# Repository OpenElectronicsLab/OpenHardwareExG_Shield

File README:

The OpenHardwareExG_Shield is a platform for ECG, EEG, EMG, ENG, EOG, and
evoked potential applications using an Arduino.

http://openelectronicslab.github.io/OpenHardwareExG_Shield/

Example firmware can be found at:

https://github.com/OpenElectronicsLab/OpenHardwareExG_Shield_Arduino_Library

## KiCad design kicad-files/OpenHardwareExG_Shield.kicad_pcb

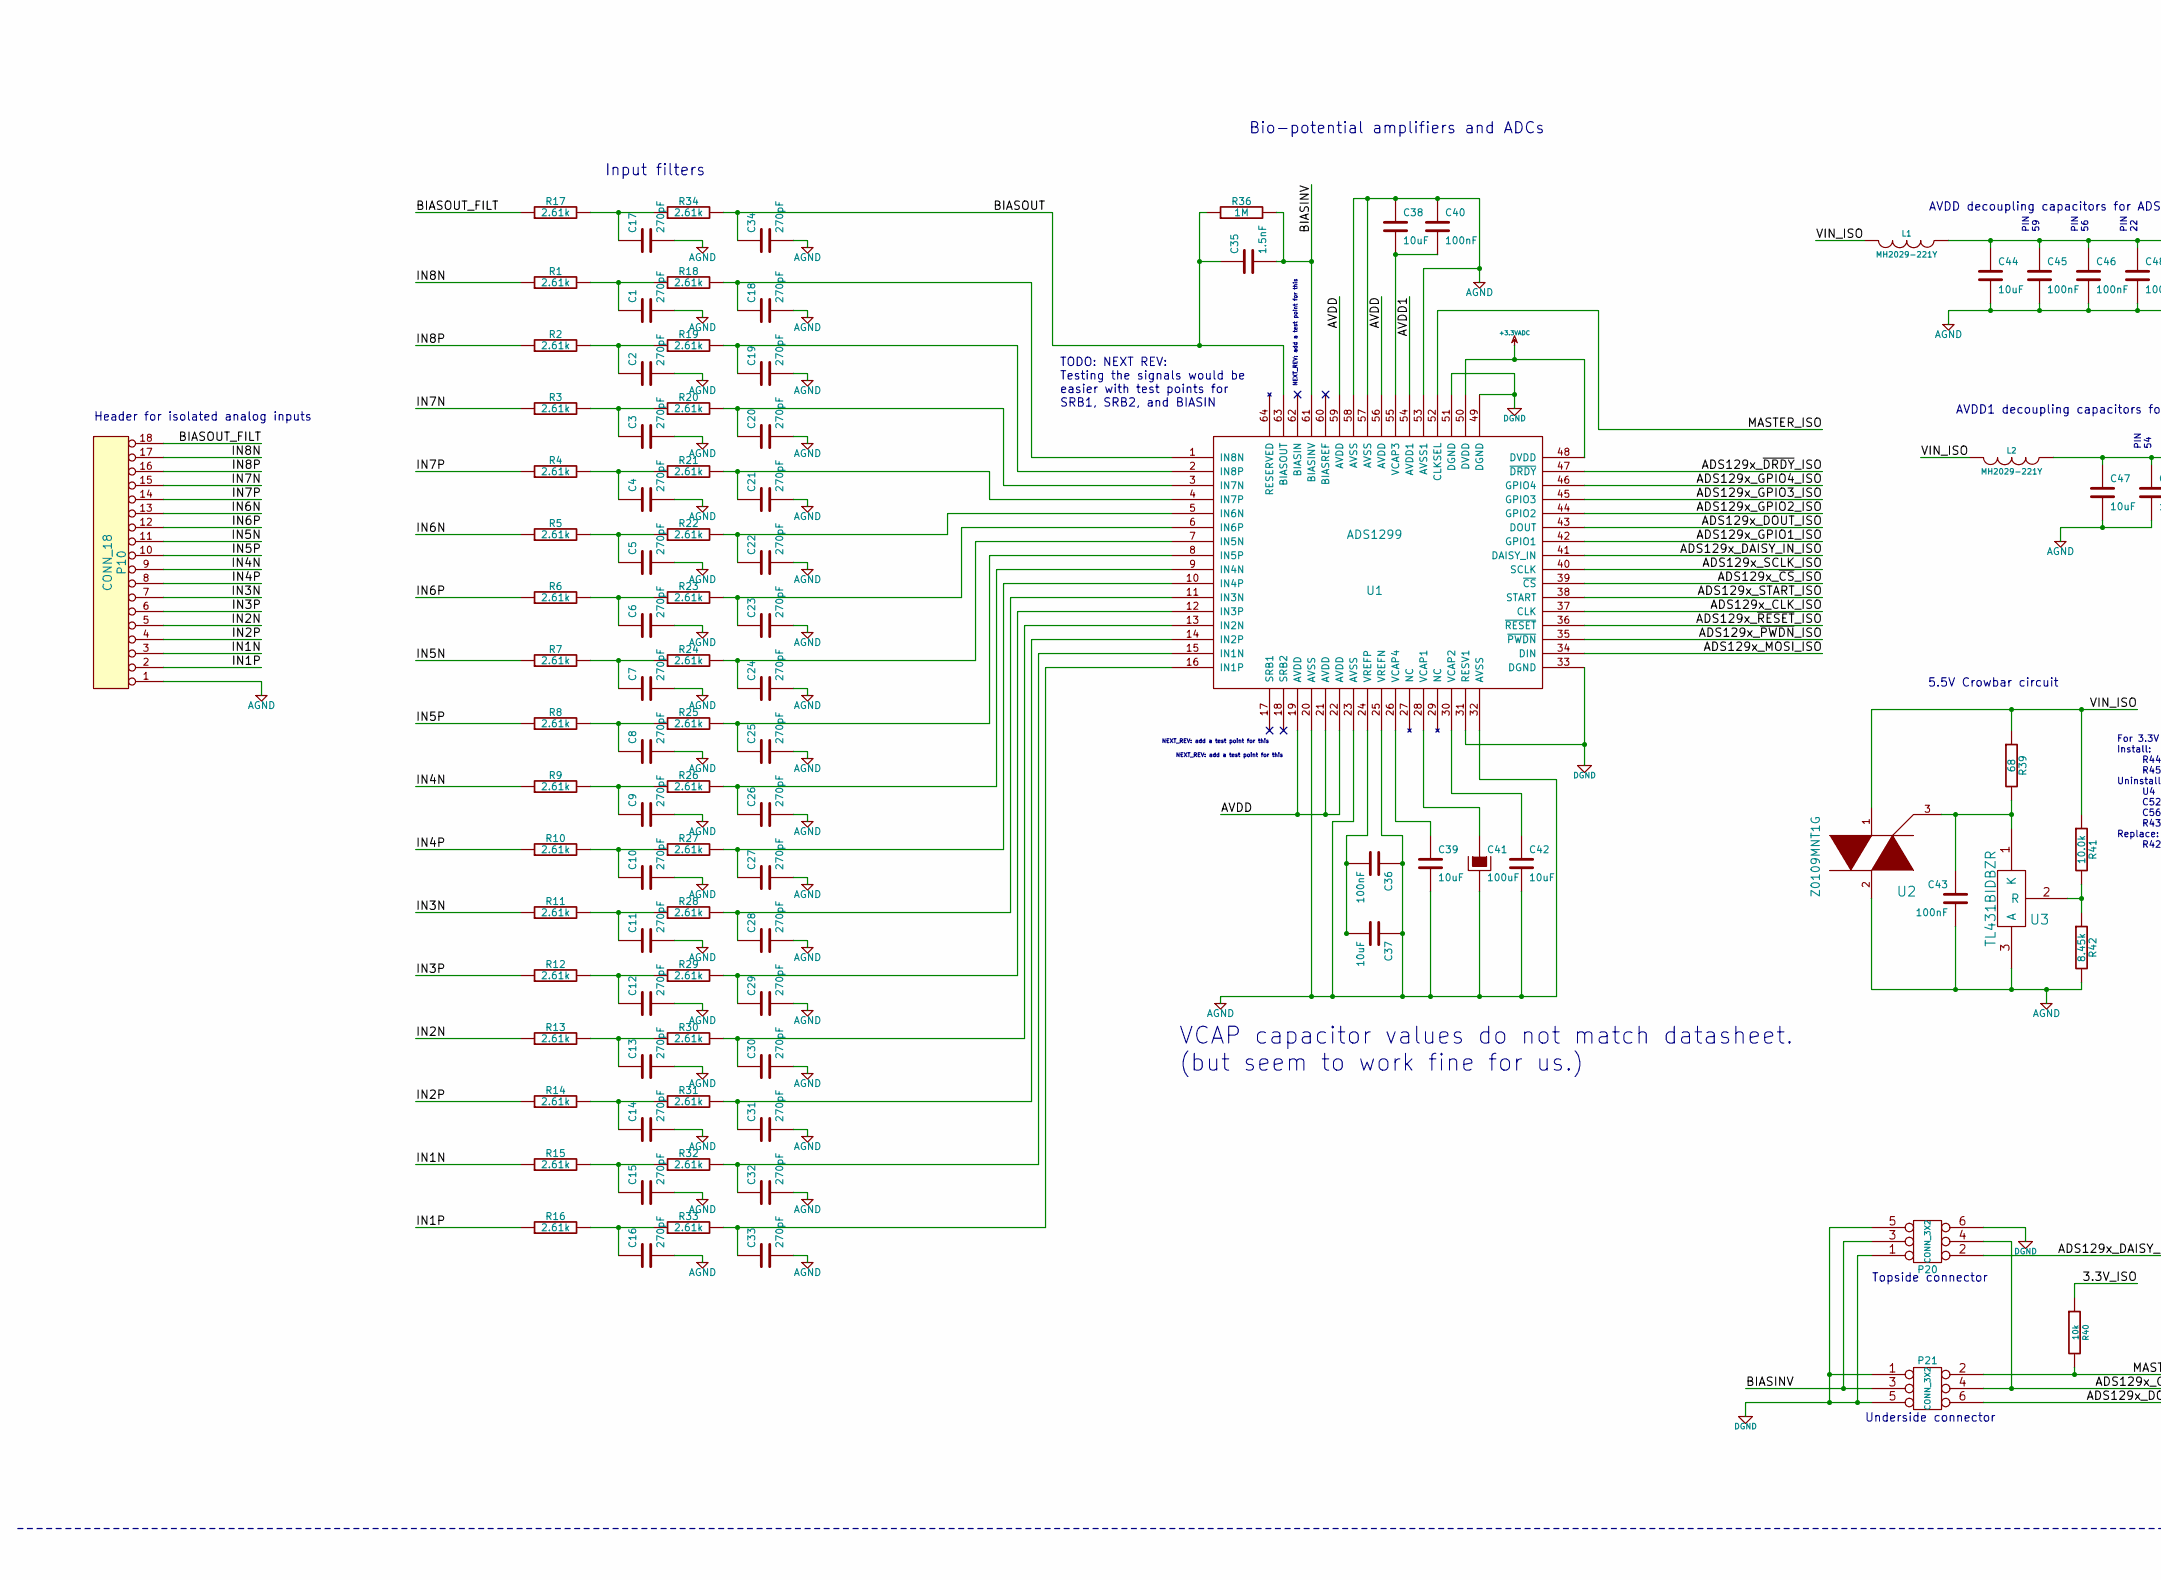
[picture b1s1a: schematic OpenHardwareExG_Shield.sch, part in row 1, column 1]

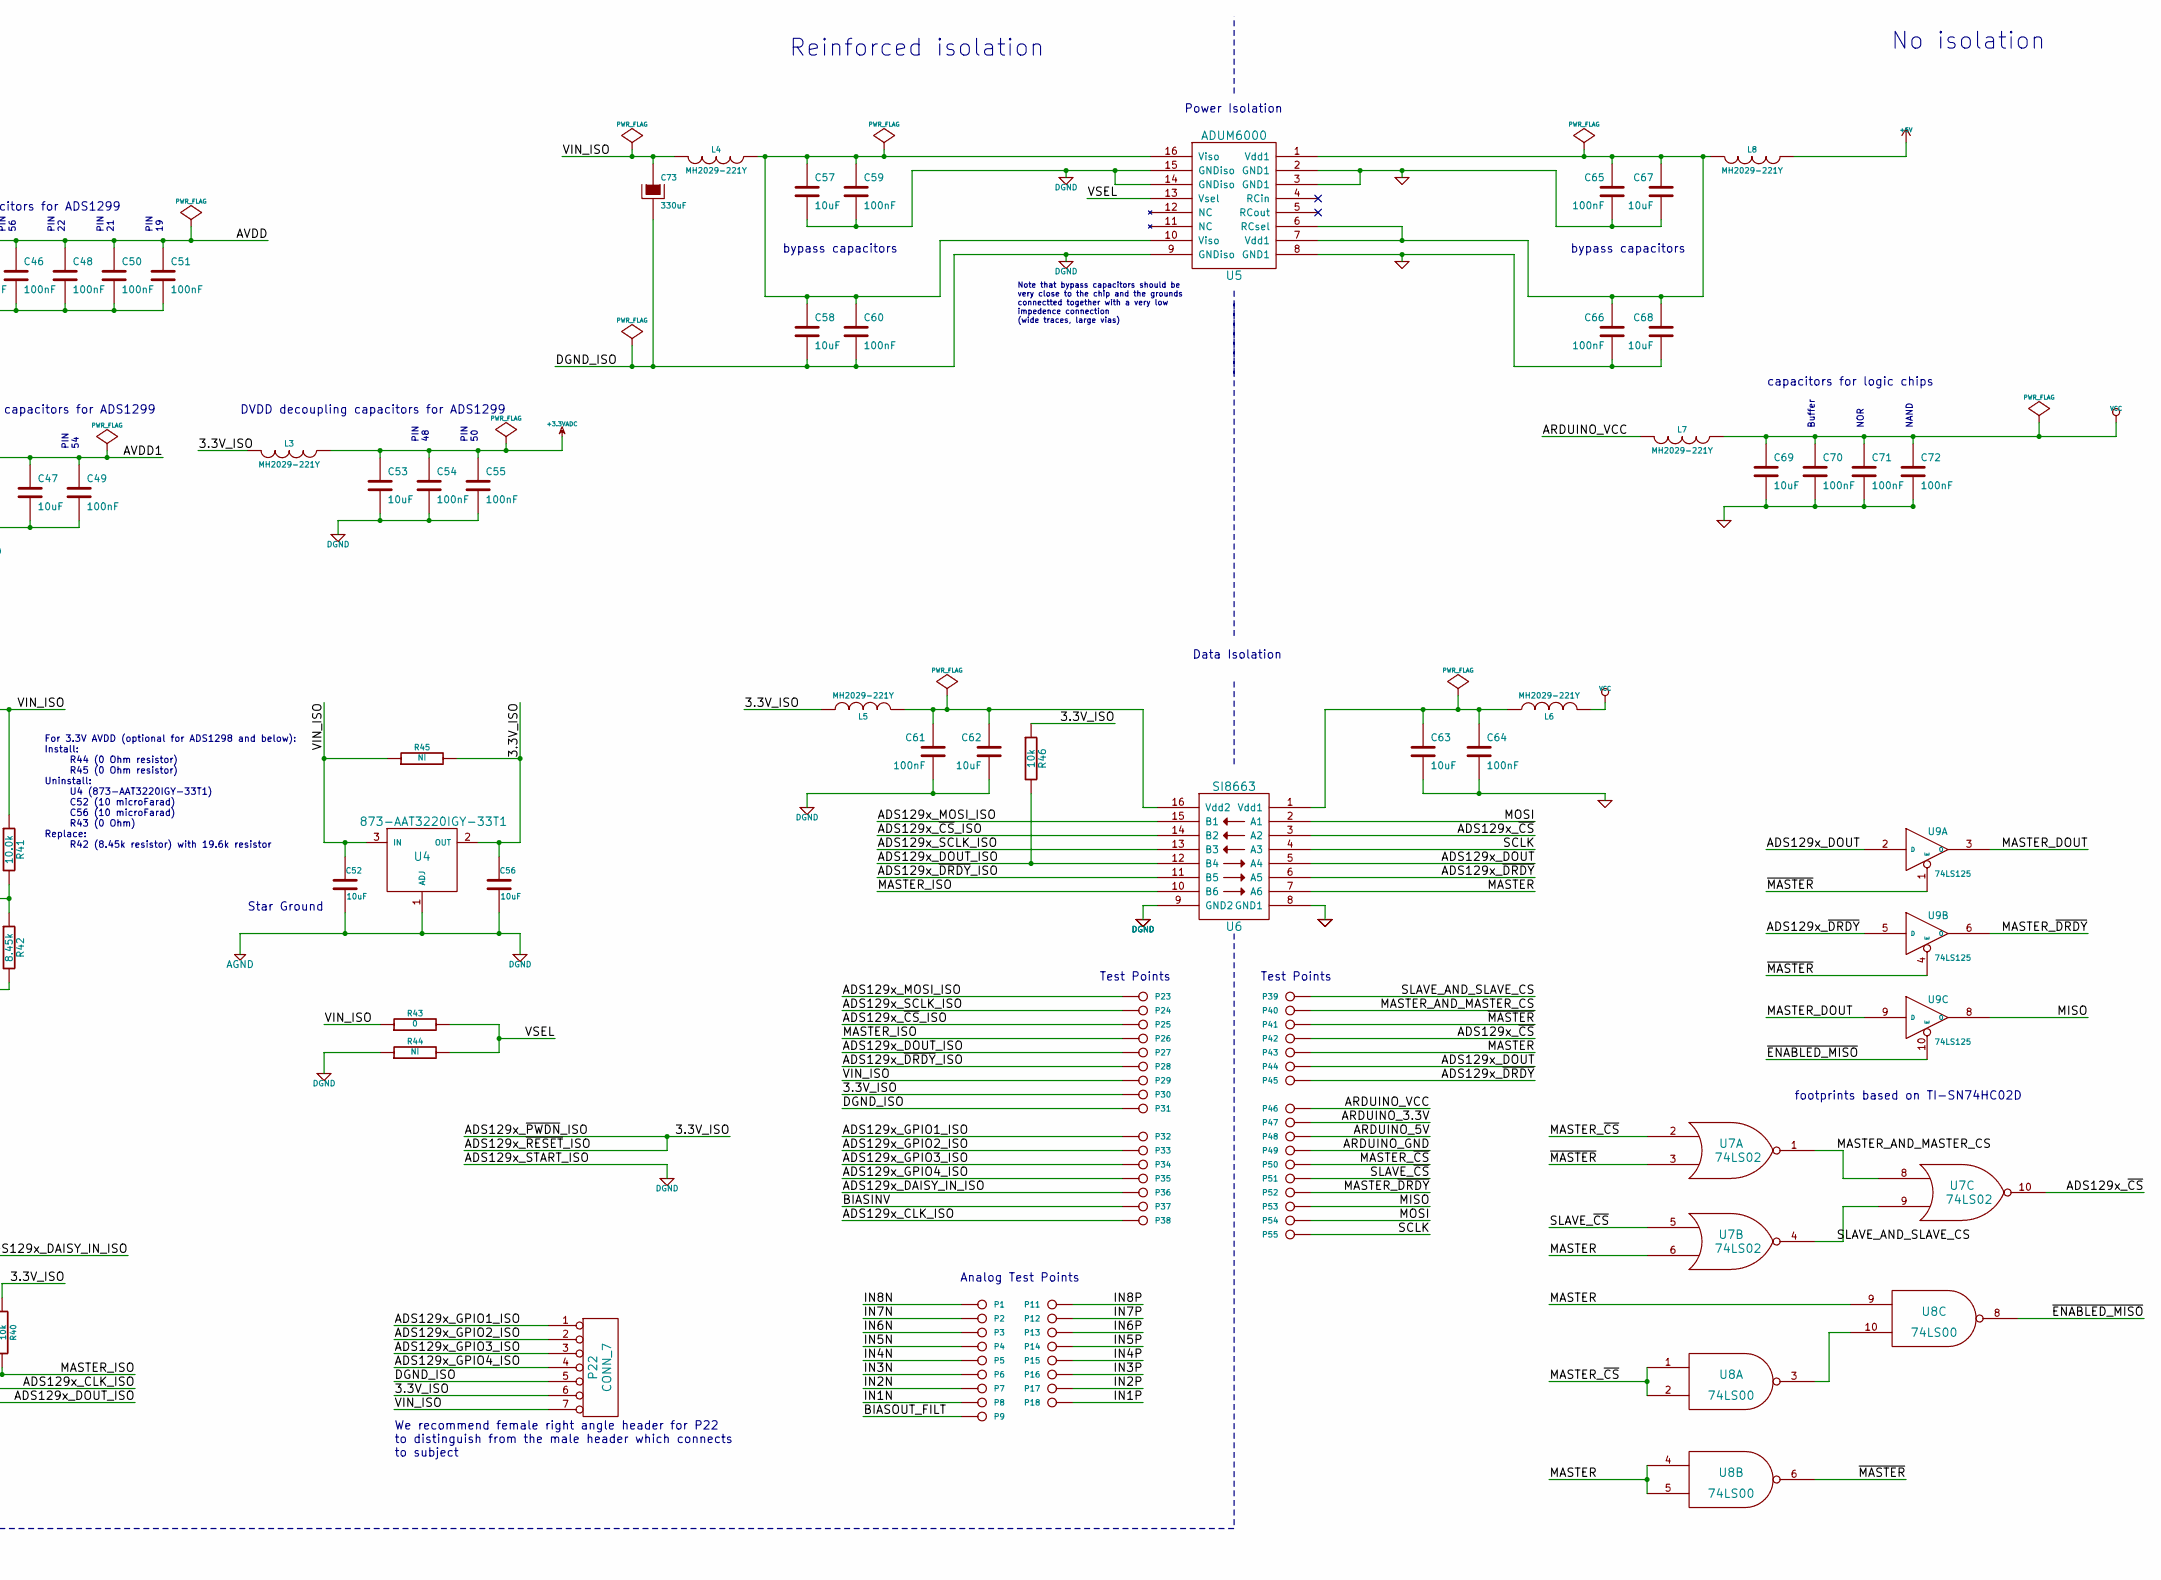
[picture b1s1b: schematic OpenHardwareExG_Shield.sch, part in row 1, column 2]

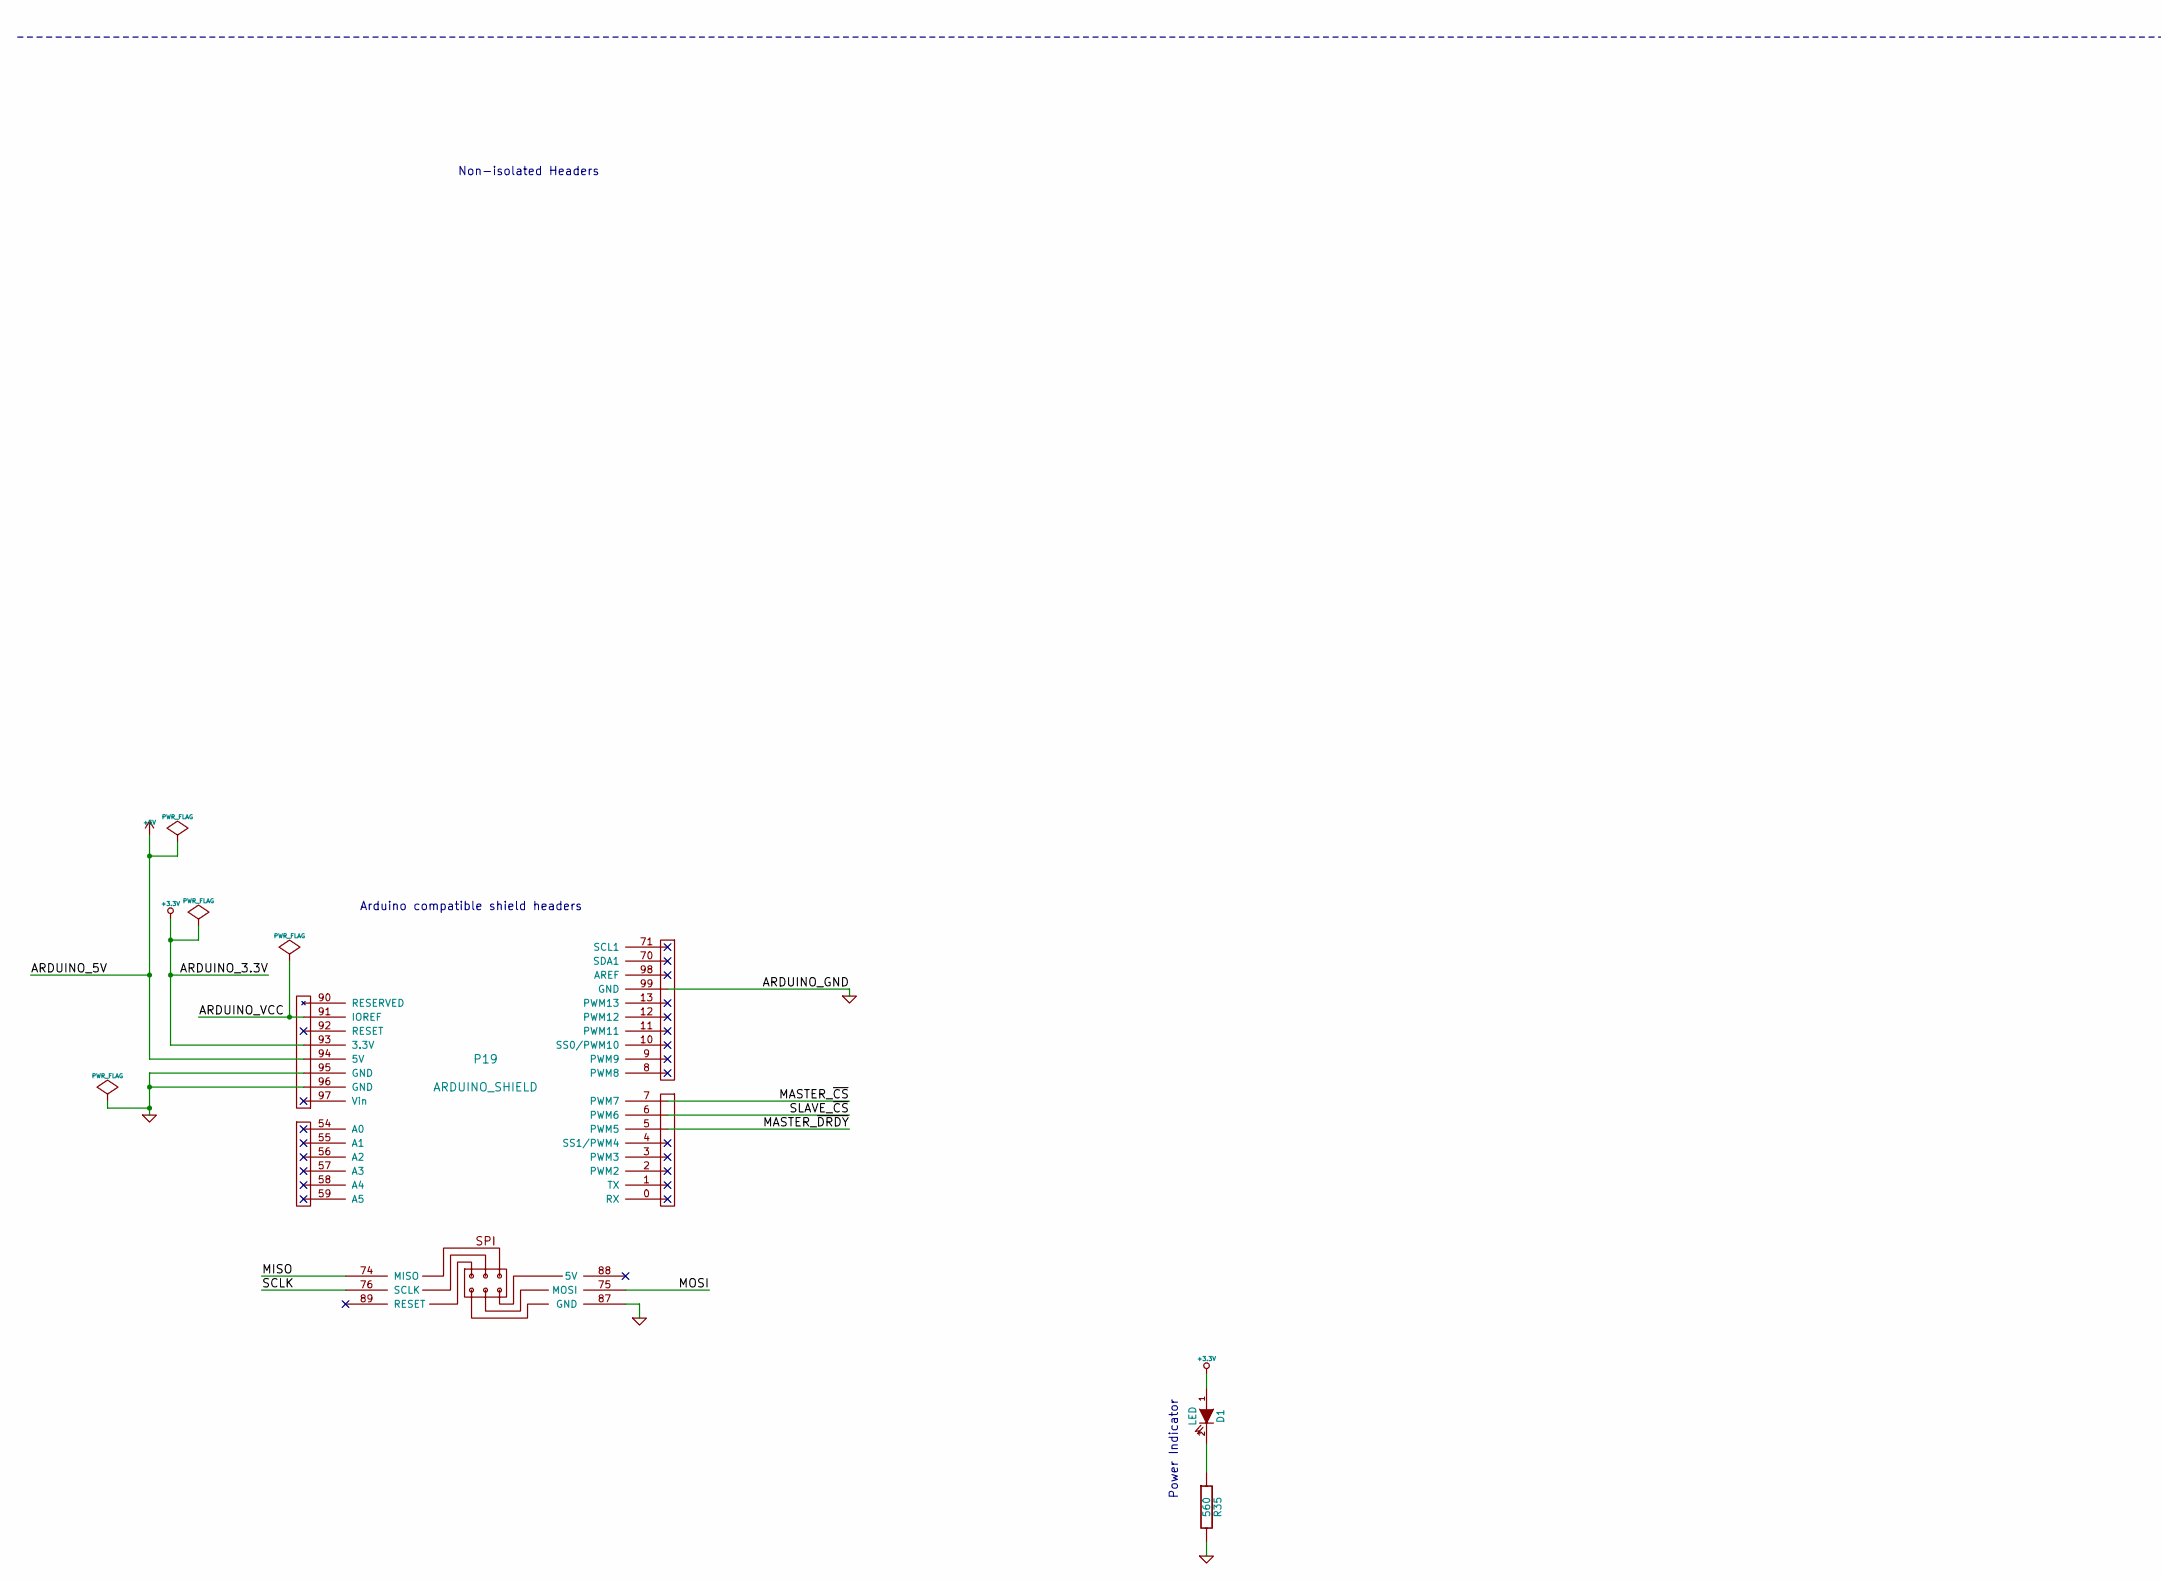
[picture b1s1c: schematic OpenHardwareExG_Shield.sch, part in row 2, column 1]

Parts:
C1, C2, C3, C4, C5, C6, C7, C8, C9, C10, C11, C12, C13, C14, C15, C16, C17, C18, C19, C20, C21, C22, C23, C24, C25, C26, C27, C28, C29, C30, C31, C32, C33, C34: 270pF; SM0603
C35: 1.5nF; SM0603
C36, C40, C43, C45, C46, C48, C49, C50, C51, C54, C55, C59, C60, C61, C64, C65, C66, C70, C71, C72: 100nF; SM0603
C37, C38, C39, C42, C44, C47, C52, C53, C56, C57, C58, C62, C63, C67, C68, C69: 10uF; SM0805
C41: 100uF; SM2512
C73: 330uF; c_tant_D
D1: LED; LED-0603
L1, L2, L3, L4, L5, L6, L7, L8: MH2029-221Y; SM0805
P1, P2, P3, P4, P5, P6, P7, P8, P9, P11, P12, P13, P14, P15, P16, P17, P18, P23, P24, P25, P26, P27, P28, P29, P30, P31, P32, P33, P34, P35, P36, P37, P38, P39, P40, P41, P42, P43, P44, P45, P46, P47, P48, P49, P50, P51, P52, P53, P54, P55: CONN_1; POGO_PAD
P10: CONN_18; PIN_ARRAY_18x1
P19: ARDUINO_SHIELD; arduino_shield_with_holes
P20: CONN_3X2; 54202-G0803ALF
P21: CONN_3X2; 89898-303LF
P22: CONN_7; PIN_ARRAY_7x1
R1, R2, R3, R4, R5, R6, R7, R8, R9, R10, R11, R12, R13, R14, R15, R16, R17, R18, R19, R20, R21, R22, R23, R24, R25, R26, R27, R28, R29, R30, R31, R32, R33, R34: 2.61k; SM0603
R35: 560; SM0603
R36: 1M; SM0805
R39: 68; SM0603
R40, R46: 10k; SM0603
R41: 10.0k; SM0603
R42: 8.45k; SM0603
R43: 0; SM0603
R44, R45: NI; SM0603
U1: ADS1299; TQFP_64
U2: Z0109MNT1G; SOT223
U3: TL431BIDBZR; SOT23
U4: 873-AAT3220IGY-33T1; SOT23
U5: ADUM6000; SO16W
U6: SI8663; SO16W
U7: 74LS02; SO14E
U8: 74LS00; SO14E
U9: 74LS125; SO14E

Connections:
+3.3V: D1.1 (A), P19.93 (3.3V), P47.1
+3.3VADC: C53.1, C54.1, C55.1, L3.1, U1.48 (DVDD), U1.50 (DVDD)
+5V: L8.2, P19.94 (5V), P48.1
/3.3V_ISO: C56.1, L3.2, L5.2, P22.6, P30.1, R40.1, R45.2, R46.1, U1.35 (~PWDN~), U1.36 (~RESET~), U4.2 (OUT)
/ADS129x_CLK_ISO: P20.4, P21.4, P38.1, U1.37 (CLK)
/ADS129x_DAISY_IN_ISO: P20.2, P36.1, U1.41 (DAISY_IN)
/ADS129x_DOUT: P44.1, U6.5 (A4), U9.2 (D)
/ADS129x_DOUT_ISO: P21.6, P27.1, R46.2, U1.43 (DOUT), U6.12 (B4)
/ADS129x_GPIO1_ISO: P22.1, P32.1, U1.42 (GPIO1); also elsewhere on the board
/ADS129x_GPIO2_ISO: P22.2, P33.1, U1.44 (GPIO2); also elsewhere on the board
/ADS129x_GPIO3_ISO: P22.3, P34.1, U1.45 (GPIO3); also elsewhere on the board
/ADS129x_GPIO4_ISO: P22.4, P35.1, U1.46 (GPIO4); also elsewhere on the board
/ADS129x_MOSI_ISO: P23.1, U1.34 (DIN), U6.15 (B1)
/ADS129x_SCLK_ISO: P24.1, U1.40 (SCLK), U6.13 (B3)
/ADS129x_~CS~: P42.1, U6.3 (A2), U7.10
/ADS129x_~CS~_ISO: P25.1, U1.39 (~CS~), U6.14 (B2)
/ADS129x_~DRDY~: P45.1, U6.6 (A5), U9.5 (D)
/ADS129x_~DRDY~_ISO: P28.1, U1.47 (~DRDY~), U6.11 (B5)
/ARDUINO_VCC: L7.2, P19.91 (IOREF), P46.1
/AVDD: C44.1, C45.1, C46.1, C48.1, C50.1, C51.1, L1.1, U1.19 (AVDD), U1.21 (AVDD), U1.22 (AVDD), U1.56 (AVDD), U1.59 (AVDD)
/AVDD1: C47.1, C49.1, L2.1, U1.54 (AVDD1)
/BIASINV: C35.2, P20.3, P21.3, P37.1, R36.2, U1.61 (BIASINV)
/BIASOUT: C34.1, C35.1, R34.2, R36.1, U1.63 (BIASOUT)
/BIASOUT_FILT: P9.1, P10.18, R17.1
/IN1N: P8.1, P10.3, R15.1
/IN1P: P10.2, P18.1, R16.1
/IN2N: P7.1, P10.5, R13.1
/IN2P: P10.4, P17.1, R14.1
/IN3N: P6.1, P10.7, R11.1
/IN3P: P10.6, P16.1, R12.1
/IN4N: P5.1, P10.9, R9.1
/IN4P: P10.8, P15.1, R10.1
/IN5N: P4.1, P10.11, R7.1
/IN5P: P10.10, P14.1, R8.1
/IN6N: P3.1, P10.13, R5.1
/IN6P: P10.12, P13.1, R6.1
/IN7N: P2.1, P10.15, R3.1
/IN7P: P10.14, P12.1, R4.1
/IN8N: P1.1, P10.17, R1.1
/IN8P: P10.16, P11.1, R2.1
/MASTER: P43.1, U6.7 (A6), U7.6, U8.4, U8.5, U8.9
/MASTER_AND_MASTER_CS: P40.1, U7.1, U7.8
/MASTER_DOUT: U9.3 (O), U9.9 (D)
/MASTER_ISO: P21.2, P26.1, R40.2, U1.52 (CLKSEL), U6.10 (B6)
/MASTER_~CS~: P19.7 (PWM7), P50.1, U7.2, U8.1, U8.2
/MASTER_~DRDY~: P19.5 (PWM5), P52.1, U9.6 (O)
/MISO: P19.74 (MISO), P53.1, U9.8 (O)
/MOSI: P19.75 (MOSI), P54.1, U6.2 (A1)
/SCLK: P19.76 (SCLK), P55.1, U6.4 (A3)
/SLAVE_AND_SLAVE_CS: P39.1, U7.4, U7.9
/SLAVE_~CS~: P19.6 (PWM6), P51.1, U7.5
/VIN_ISO: C52.1, C73.1, L1.2, L2.2, L4.2, P22.7, P29.1, R39.1, R41.1, R43.1, R45.1, U2.1, U4.3 (IN)
/VSEL: R43.2, R44.2, U5.13 (Vsel)
/~ENABLED_MISO~: U8.8, U9.10 (E)
/~MASTER~: P41.1, U7.3, U8.6, U9.1 (E), U9.4 (E)
AGND: C1.2, C2.2, C3.2, C4.2, C5.2, C6.2, C7.2, C8.2, C9.2, C10.2, C11.2, C12.2, C13.2, C14.2, C15.2, C16.2, C17.2, C18.2, C19.2, C20.2, C21.2, C22.2, C23.2, C24.2, C25.2, C26.2, C27.2, C28.2, C29.2, C30.2, C31.2, C32.2, C33.2, C34.2, C36.1, C37.1, C38.1, C39.2, C40.1, C41.2, C42.2, C43.2, C44.2, C45.2, C46.2, C47.2, C48.2, C49.2, C50.2, C51.2, C52.2, C53.2, C54.2, C55.2, C56.2, C57.2, C58.2, C59.2, C60.2, C61.2, C62.2, C73.2, P10.1, P20.1, P20.5, P20.6, P21.1, P21.5, P22.5, P31.1, R42.2, R44.1, U1.20 (AVSS), U1.23 (AVSS), U1.25 (VREFN), U1.31 (RESV1), U1.32 (AVSS), U1.33 (DGND), U1.38 (START), U1.49 (DGND), U1.51 (DGND), U1.53 (AVSS1), U1.57 (AVSS), U1.58 (AVSS), U2.2, U3.3 (A), U4.1 (ADJ), U5.9 (GNDiso), U5.14 (GNDiso), U5.15 (GNDiso), U6.9 (GND2); also elsewhere on the board
GND: C63.2, C64.2, C65.2, C66.2, C67.2, C68.2, C69.2, C70.2, C71.2, C72.2, P19.87 (GND), P19.95 (GND), P19.96 (GND), P19.99 (GND), P49.1, R35.2, U5.2 (GND1), U5.3 (GND1), U5.8 (GND1), U6.8 (GND1), U7.7 (GND), U8.7 (GND), U9.7 (GND)
unnamed: C1.1, R1.2, R18.1
unnamed: C2.1, R2.2, R19.1
unnamed: C3.1, R3.2, R20.1
unnamed: C4.1, R4.2, R21.1
unnamed: C5.1, R5.2, R22.1
unnamed: C6.1, R6.2, R23.1
unnamed: C7.1, R7.2, R24.1
unnamed: C8.1, R8.2, R25.1
unnamed: C9.1, R9.2, R26.1
unnamed: C10.1, R10.2, R27.1
unnamed: C11.1, R11.2, R28.1
unnamed: C12.1, R12.2, R29.1
unnamed: C13.1, R13.2, R30.1
unnamed: C14.1, R14.2, R31.1
unnamed: C15.1, R15.2, R32.1
unnamed: C16.1, R16.2, R33.1
unnamed: C17.1, R17.2, R34.1
unnamed: C18.1, R18.2, U1.1 (IN8N)
unnamed: C19.1, R19.2, U1.2 (IN8P)
unnamed: C20.1, R20.2, U1.3 (IN7N)
unnamed: C21.1, R21.2, U1.4 (IN7P)
unnamed: C22.1, R22.2, U1.5 (IN6N)
unnamed: C23.1, R23.2, U1.6 (IN6P)
unnamed: C24.1, R24.2, U1.7 (IN5N)
unnamed: C25.1, R25.2, U1.8 (IN5P)
unnamed: C26.1, R26.2, U1.9 (IN4N)
unnamed: C27.1, R27.2, U1.10 (IN4P)
unnamed: C28.1, R28.2, U1.11 (IN3N)
unnamed: C29.1, R29.2, U1.12 (IN3P)
unnamed: C30.1, R30.2, U1.13 (IN2N)
unnamed: C31.1, R31.2, U1.14 (IN2P)
unnamed: C32.1, R32.2, U1.15 (IN1N)
unnamed: C33.1, R33.2, U1.16 (IN1P)
unnamed: C36.2, C37.2, U1.24 (VREFP)
unnamed: C38.2, C40.2, U1.55 (VCAP3)
unnamed: C39.1, U1.26 (VCAP4)
unnamed: C41.1, U1.28 (VCAP1)
unnamed: C42.1, U1.30 (VCAP2)
unnamed: C43.1, R39.2, U2.3, U3.1 (K)
unnamed: C57.1, C58.1, C59.1, C60.1, L4.1, U5.10 (Viso), U5.16 (Viso)
unnamed: C61.1, C62.1, L5.1, U6.16 (Vdd2)
unnamed: C63.1, C64.1, L6.1, U6.1 (Vdd1)
unnamed: C65.1, C66.1, C67.1, C68.1, L8.1, U5.1 (Vdd1), U5.6 (RCsel), U5.7 (Vdd1)
unnamed: D1.2 (K), R35.1
unnamed: R41.2, R42.1, U3.2 (R)
unnamed: U8.3, U8.10
VCC: C69.1, C70.1, C71.1, C72.1, L6.2, L7.1, U7.14 (VCC), U8.14 (VCC), U9.14 (VCC)

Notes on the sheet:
Power Indicator
Non-isolated Headers
Arduino compatible shield headers
Header for isolated analog inputs
Input filters
Bio-potential amplifiers and ADCs
5.5V Crowbar circuit
No isolation
Reinforced isolation
PIN 48
PIN 50
DVDD decoupling capacitors for ADS1299
Data Isolation
Power Isolation
AVDD1 decoupling capacitors for ADS1299
PIN 54
PIN 19
PIN 21
PIN 22
PIN 56
PIN 59
AVDD decoupling capacitors for ADS1299
Underside connector
Topside connector
NAND
NOR
Buffer
capacitors for logic chips
Note that bypass capacitors should be very close to the chip and the grounds connectted together with a very low impedence connection (wide traces, large vias)
bypass capacitors
Test Points
Analog Test Points
footprints based on TI-SN74HC02D
Star Ground
For 3.3V AVDD (optional for ADS1298 and below): Install: R44 (0 Ohm resistor) R45 (0 Ohm resistor) Uninstall: U4 (873-AAT3220IGY-33T1) C52 (10 microFarad) C56 (10 microFarad) R43 (0 Ohm) Replace: R42 (8.45k resistor) with 19.6k resistor
VCAP capacitor values do not match datasheet. (but seem to work fine for us.)
We recommend female right angle header for P22 to distinguish from the male header which connects to subject
NEXT_REV: add a test point for this
TODO: NEXT REV: Testing the signals would be easier with test points for SRB1, SRB2, and BIASIN

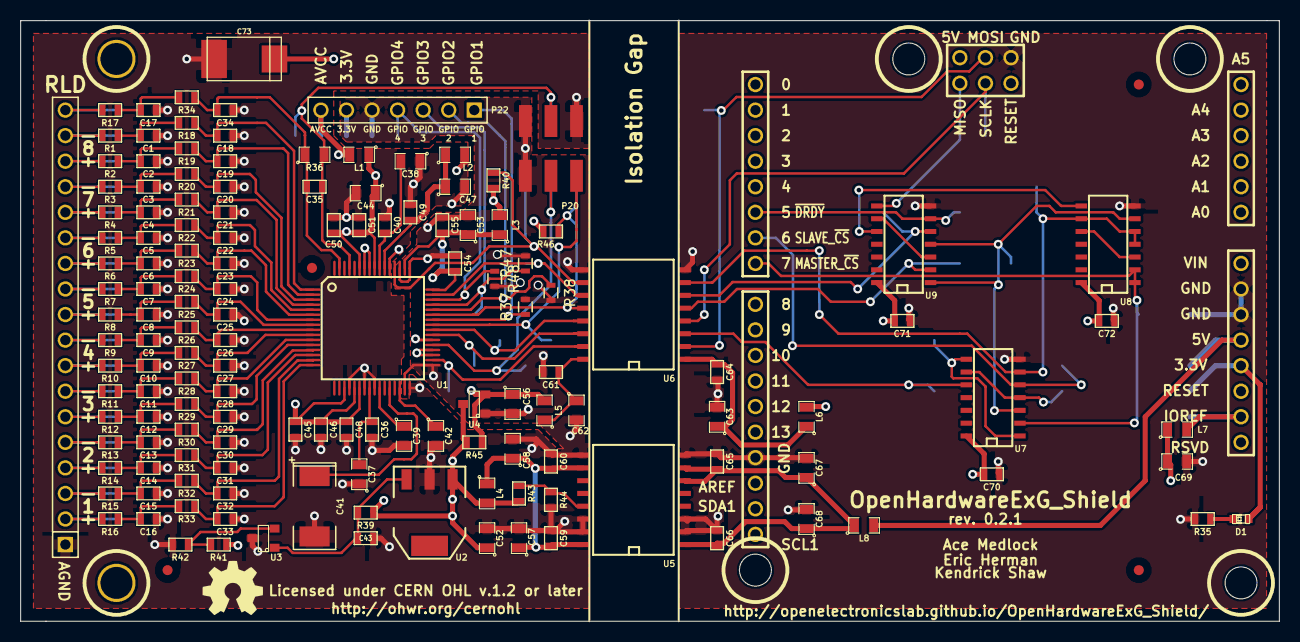
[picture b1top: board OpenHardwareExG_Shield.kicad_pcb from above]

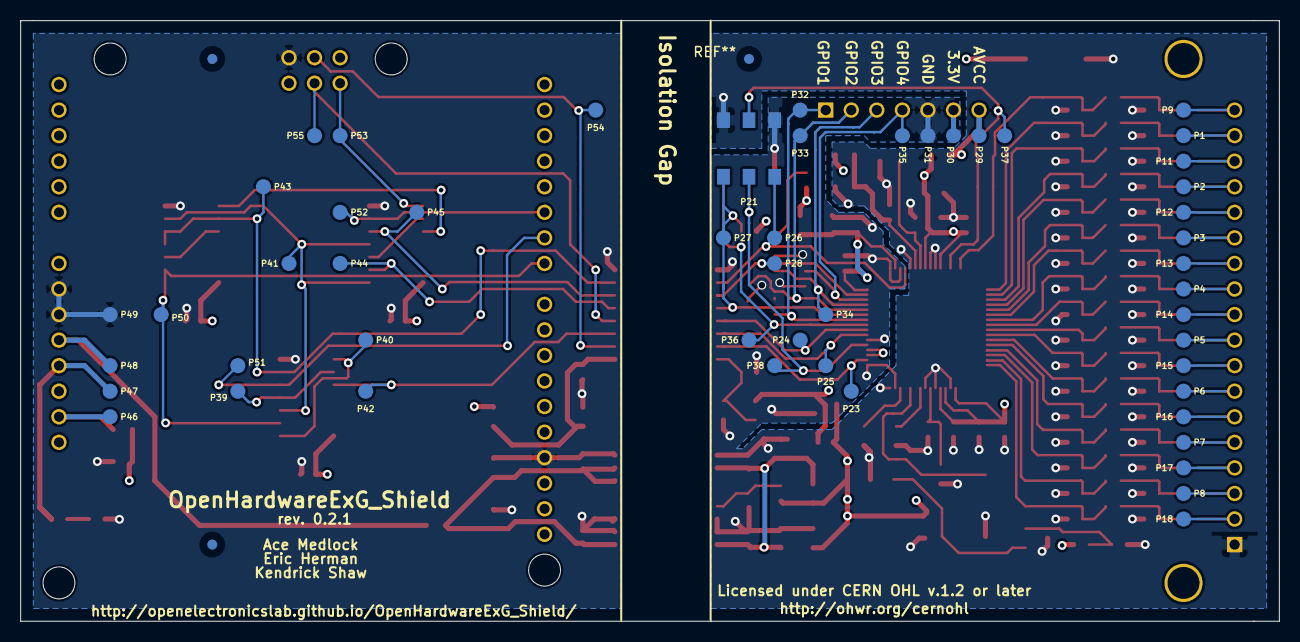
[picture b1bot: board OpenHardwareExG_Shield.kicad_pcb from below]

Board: 4 copper layers, 125.1 x 59.7 mm, 196 parts (51 on the bottom side), 104 nets.

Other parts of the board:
Hole_M3, Hole_M3#2: VAL**; Hole_M3
R37, R38, R47, R48: 10k; R_0603

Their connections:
/ADS129x_GPIO1_ISO: R37.1; also elsewhere on the board
/ADS129x_GPIO2_ISO: R38.1; also elsewhere on the board
/ADS129x_GPIO3_ISO: R47.1; also elsewhere on the board
/ADS129x_GPIO4_ISO: R48.1; also elsewhere on the board
AGND: R37.2, R38.2, R47.2, R48.2; also elsewhere on the board

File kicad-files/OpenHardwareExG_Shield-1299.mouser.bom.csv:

mfg part number  ,  quantity 1  ,  Description  ,  Customer Part No.
VJ0805A271KXBPW1BC  ,  34  ,  270pF  ,  C1-34
CGA3E2X7R1H152K080AA  ,  1  ,  1.5nF  ,  C35
VJ0603Y104JXJPW1BC  ,  19  ,  100nF  ,  C36_C40_C45-46_C48-51_C54-55_C59-61_C64-66_C70-72
GRM21BR71A106KA73L  ,  17  ,  10uF  ,  C37-39_C42-44_C47_C52-53_C56-58_C62-63_C67-69
593D107X9010C2TE3  ,  1  ,  100uF  ,  C41
LG Q971-KN-1  ,  1  ,  LED  ,  D1
MH2029-221Y  ,  8  ,  MH2029-221Y  ,  L1-8
68021-120HLF  ,  1  ,  CONN_10X2  ,  P10
54202-G0803ALF  ,  1  ,  CONN_3X2  ,  P20
89898-303LF  ,  1  ,  CONN_3X2  ,  P21
RR1220P-2611-D-M  ,  34  ,  2.61k  ,  R1-34
CRCW0603560RJNEA  ,  1  ,  560  ,  R35
RR1220P-105-D  ,  1  ,  1M  ,  R36
CRCW060347R0FKEA  ,  6  ,  47  ,  R37-38_R47-50
CRCW060368R0JNEA  ,  1  ,  68  ,  R39
RR0816P-103-D  ,  3  ,  10k  ,  R40-41_R46
RR0816P-8451-D-90H  ,  1  ,  8.45k  ,  R42
CRCW06030000Z0EB  ,  1  ,  0  ,  R43
ADS1299IPAG  ,  1  ,  ADS1299  ,  U1
Z0109MNT1G  ,  1  ,  Z0109MNT1G  ,  U2
771-TL431BIDBZR215  ,  1  ,  TL431BIDBZR  ,  U3
873-AAT3220IGY-33T1  ,  1  ,  873-AAT3220IGY-33T1  ,  U4
ADUM6000ARIZ  ,  1  ,  ADUM6000  ,  U5
Si8663BD-B-IS  ,  1  ,  SI8663  ,  U6
MC74HC02ADG  ,  1  ,  74LS02  ,  U7
MC74HC00ADR2G  ,  1  ,  74LS00  ,  U8
MC74HC125ADG  ,  1  ,  74LS125  ,  U9

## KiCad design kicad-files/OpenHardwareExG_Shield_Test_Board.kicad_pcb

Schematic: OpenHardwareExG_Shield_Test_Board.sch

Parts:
C1, C5, C10, C11: 10uF; SM0805
C2, C3, C4, C6, C7, C8, C9, C12: 100nF; SM0603
D1, D2, D3: LED; LED-0603
L1, L3, L4: MH2029-221Y; SM0805
P1, P2, P3, P4, P5, P6, P7, P8, P9, P11, P12, P13, P14, P15, P16, P17, P18, P23, P24, P25, P26, P27, P28, P29, P30, P31, P32, P33, P34, P35, P36, P37, P38, P39, P40, P41, P42, P43, P44, P45, P46, P47, P48, P49, P50, P51, P52, P53, P54, P55: CONN_1; POGO_PIN_BASE
P19: ARDUINO_SHIELD; arduino_shield_with_holes
P56: CONN_3X2; pin_array_3x2
P57: CONN_20X2; PIN_ARRAY_20X2
R1, R3, R5, R43, R44: 10k; SM0603
R2, R4, R6: 1k; SM0603
R7: 5.1K; SM0603
R8, R18, R19, R20, R21, R22, R23, R24, R25, R26, R27, R28, R29, R30, R31, R32: 100; SM0603
R9, R10, R11, R12, R13, R14, R15, R16, R34, R35, R36, R37, R38, R39: 1M; SM0805
R17, R33: 15k; SM0603
R40, R41, R42: 560; SM0603
SW1: SW_PUSH; smt-tactile-button
U1, U2, U4: 74HC165; SO16E
U3: 74HC595PWR; TSSOP16
U5: 74LS125; SO14E
U6: TPS2095D; SO16E
U8: SI8661; SO16W

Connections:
+3.3V: P19.93 (3.3V), U6.3 (IN2)
+5V: P19.88 (5V), P19.94 (5V), P56.4, U6.6 (IN3)
/3.3V_BOGUS_ISO: L1.2, P30.1, P57.3, P57.4, R3.1
/3.3V_BOGUS_ISO_DATA: C9.1, C10.1, L3.1, U8.16
/A1: P19.55 (A1), R5.2, R6.1
/A2: P19.56 (A2), R3.2, R4.1
/A3: P19.57 (A3), R1.2, R2.1
/A4: P19.58 (A4), R8.2
/ADS129x_CLK_BOGUS_ISO: P38.1, R35.1, U2.13 (C)
/ADS129x_DAISY_IN_BOGUS_ISO: P36.1, R34.1, U1.13 (C)
/ADS129x_DOUT: P44.1, U4.12 (B)
/ADS129x_DOUT_BOGUS_ISO: P27.1, R39.1, U2.11 (A)
/ADS129x_GPIO1_BOGUS_ISO: P32.1, R9.1, U1.3 (E)
/ADS129x_GPIO2_BOGUS_ISO: P33.1, R11.1, U1.4 (F)
/ADS129x_GPIO3_BOGUS_ISO: P34.1, R13.1, U1.5 (G)
/ADS129x_GPIO4_BOGUS_ISO: P35.1, R15.1, U1.6 (H)
/ADS129x_MOSI_BOGUS_ISO: P23.1, R10.1, U2.3 (E)
/ADS129x_SCLK_BOGUS_ISO: P24.1, R12.1, U2.4 (F)
/ADS129x_~CS~: P42.1, U4.14 (D)
/ADS129x_~CS~_BOGUS_ISO: P25.1, R14.1, U2.5 (G)
/ADS129x_~DRDY~: P45.1, U4.11 (A)
/ADS129x_~DRDY~_BOGUS_ISO: P28.1, R37.1, U2.12 (B)
/ARDUINO_VCC: C5.1, C6.1, C7.1, C8.1, D1.1 (A), L4.2, P19.91 (IOREF), P56.2, R44.2, SW1.2, U3.16 (VCC), U4.16 (VCC), U6.2 (IN1)
/BIASINV: P37.1, R36.1, U1.12 (B)
/BIASOUT_FILT: P9.1, P19.59 (A5), R7.1
/ENABLE_SHIELD: U3.7 (QH), U6.4 (EN1), U6.8 (EN3), U6.13 (EN2)
/FAULT_LED: D3.1 (A), U3.6 (QG)
/GO_BUTTON: R43.1, SW1.1, U4.6 (H)
/IN1N: P8.1, P57.37
/IN1N_LADDER: P57.38, R31.2, R32.2
/IN1P: P18.1, P57.39
/IN1P_LADDER: P57.40, R32.1, R33.1
/IN2N: P7.1, P57.33
/IN2N_LADDER: P57.34, R29.2, R30.2
/IN2P: P17.1, P57.35
/IN2P_LADDER: P57.36, R30.1, R31.1
/IN3N: P6.1, P57.29
/IN3N_LADDER: P57.30, R27.2, R28.2
/IN3P: P16.1, P57.31
/IN3P_LADDER: P57.32, R28.1, R29.1
/IN4N: P5.1, P57.25
/IN4N_LADDER: P57.26, R25.2, R26.2
/IN4P: P15.1, P57.27
/IN4P_LADDER: P57.28, R26.1, R27.1
/IN5N: P4.1, P57.21
/IN5N_LADDER: P57.22, R23.2, R24.2
/IN5P: P14.1, P57.23
/IN5P_LADDER: P57.24, R24.1, R25.1
/IN6N: P3.1, P57.17
/IN6N_LADDER: P57.18, R21.2, R22.2
/IN6P: P13.1, P57.19
/IN6P_LADDER: P57.20, R22.1, R23.1
/IN7N: P2.1, P57.13
/IN7N_LADDER: P57.14, R19.2, R20.2
/IN7P: P12.1, P57.15
/IN7P_LADDER: P57.16, R20.1, R21.1
/IN8N: P1.1, P57.9
/IN8N_LADDER: P57.10, R17.2, R18.2
/IN8P: P11.1, P57.11
/IN8P_LADDER: P57.12, R18.1, R19.1
/LED1: D1.2 (K), R40.1
/LED2: D2.2 (K), R41.1
/LED3: D3.2 (K), R42.1
/MASTER: P43.1, U4.13 (C)
/MASTER_AND_MASTER_CS: P40.1, U4.4 (F)
/MASTER_BOGUS_ISO: P26.1, R16.1, U2.6 (H), U5.3 (O)
/MASTER_~CS~: P50.1, U3.1 (QB)
/MASTER_~DRDY~: P19.2 (PWM2), P52.1
/MIDDLE_CARRY: U1.9 (QH), U2.10 (SER)
/MISO: P19.74 (MISO), P53.1
/MOSI: P19.75 (MOSI), P54.1
/SCLK: P19.76 (SCLK), P55.1
/SHIELD_3.3V: P47.1, U6.14 (OUT2)
/SHIELD_5V: P48.1, U6.11 (OUT3)
/SHIELD_VCC: P46.1, U6.15 (OUT1)
/SHIFT_CARRY: U4.10 (SER), U8.7
/SHIFT_CARRY_BOGUS_ISO: U2.9 (QH), U8.10
/SHIFT_CLK: P19.8 (PWM8), U4.2 (CLK), U8.6
/SHIFT_CLK_BOGUS_ISO: P56.3, U1.2 (CLK), U2.2 (CLK), U8.11
/SHIFT_EXT_CARRY_BOGUS_ISO: P56.5, R38.1, U1.10 (SER)
/SHIFT_IN: P19.54 (A0), U4.9 (QH)
/SHIFT_OUT: P19.6 (PWM6), U3.14 (SER)
/SHIFT_OUT_RCLK: P19.5 (PWM5), U3.12 (RCLK)
/SHIFT_OUT_SRCLK: P19.4 (SS1/PWM4), U3.11 (SRCLK)
/SHIFT_OUT_~SRCLR~: P19.3 (PWM3), U3.10 (~SRCLR~)
/SHIFT_SH_~LD~: P19.9 (PWM9), U4.1 (SH_~LD~), U8.5
/SHIFT_SH_~LD~_BOGUS_ISO: P56.1, U1.1 (SH_~LD~), U2.1 (SH_~LD~), U8.12
/SIGNAL_A: U3.3 (QD), U8.2
/SIGNAL_A_BOGUS_ISO: P57.6, U8.15
/SIGNAL_A_LADDER: P57.5, R17.1
/SIGNAL_B: U3.4 (QE), U8.3
/SIGNAL_B_BOGUS_ISO: P57.8, U8.14
/SIGNAL_B_LADDER: P57.7, R33.2
/SLAVE_AND_SLAVE_CS: P39.1, U4.3 (E)
/SLAVE_~CS~: P51.1, U3.2 (QC)
/SUCCESS_LED: D2.1 (A), U3.5 (QF)
/VCC_DATA: C11.1, C12.1, L4.1, U8.1
/VIN_BOGUS_ISO: P29.1, R5.1
/~MASTER~: P41.1, U4.5 (G)
/~SEND_TO_GND~_MASTER: U3.15 (QA), U8.4
/~SEND_TO_GND~_MASTER_BOGUS_ISO: U5.1 (E), U8.13
/~SHIELD_SHORTED~: P19.7 (PWM7), R44.1, U6.12 (~OCB~), U6.16 (~OCA~)
GND: C1.2, C2.2, C3.2, C4.2, C9.2, C10.2, P31.1, P57.1, P57.2, R1.1, R8.1, R9.2, R10.2, R11.2, R12.2, R13.2, R14.2, R15.2, R16.2, R34.2, R35.2, R36.2, R37.2, R38.2, R39.2, U1.8 (GND), U1.15 (CLK_INH), U2.8 (GND), U2.15 (CLK_INH), U5.2 (D), U5.7 (GND), U8.9
GNDPWR: C5.2, C6.2, C7.2, C8.2, C11.2, C12.2, P19.87 (GND), P19.95 (GND), P19.96 (GND), P19.99 (GND), P49.1, P56.6, R2.2, R4.2, R6.2, R7.2, R40.2, R41.2, R42.2, R43.2, U3.8 (GND), U3.13 (~OE~), U4.8 (GND), U4.15 (CLK_INH), U6.1 (GNDA), U6.5 (GNDB), U6.7 (IN4), U6.9 (EN4), U8.8
VCC: C1.1, C2.1, C3.1, C4.1, L1.1, L3.2, U1.11 (A), U1.14 (D), U1.16 (VCC), U2.14 (D), U2.16 (VCC), U5.14 (VCC)

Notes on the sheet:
Power Indicator
Non-isolated Headers
Arduino compatible shield headers
No isolation
bogus isolation
Bogus Data Isolation
Test Pogos
SHIFT
Buffer
capacitors for logic chips
Success Indicator
Fault Indicator

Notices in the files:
kicad-files/OpenHardwareExG_Shield.kicad_pcb:
Licensed under CERN OHL v.1.2 or later
kicad-files/OpenHardwareExG_Shield_Test_Board.kicad_pcb:
CERN Open Hardware License v1.2
